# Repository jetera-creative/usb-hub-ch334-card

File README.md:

# usb-hub-ch334-card
USB Hub CH334 Card.

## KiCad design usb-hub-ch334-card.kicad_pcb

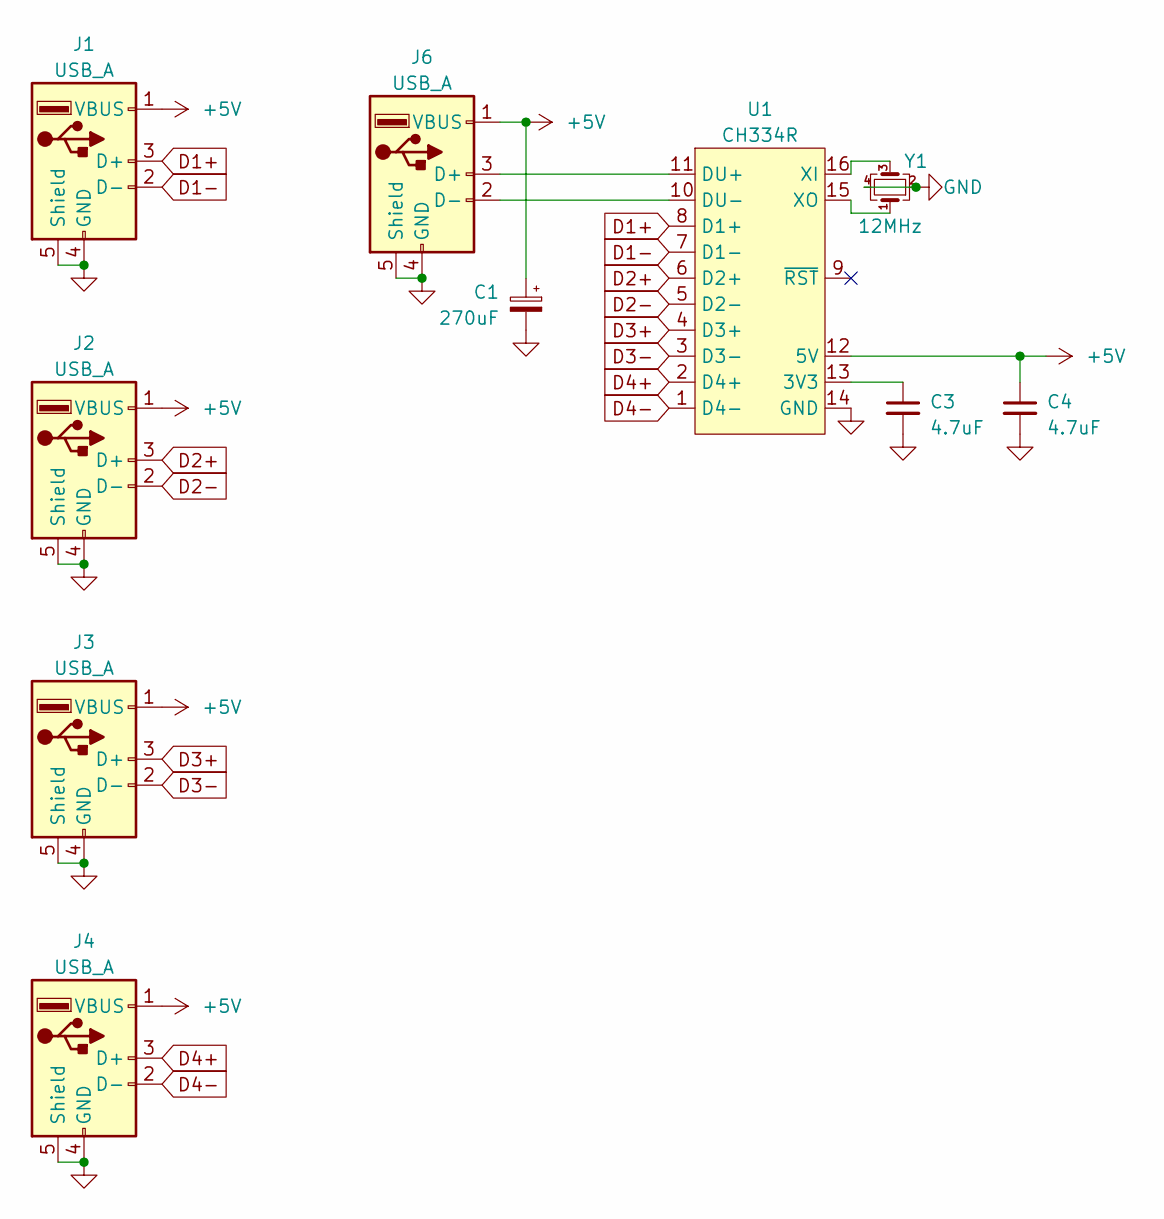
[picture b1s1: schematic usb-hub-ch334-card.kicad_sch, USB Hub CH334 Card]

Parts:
C1: 270uF; CP_Radial_D5.0mm_P2.50mm
C3, C4: 4.7uF; C_0805_2012Metric
J1, J2, J3, J4: USB_A; USB_A_Stewart_SS-52100-001_Horizontal
J6: USB_A; USB_A_Molex_48037-2200_Horizontal
U1: CH334R; QSOP-16_3.9x4.9mm_P0.635mm
Y1: 12MHz; Crystal_SMD_3225-4Pin_3.2x2.5mm

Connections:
+5V: C1.1, C4.1, J1.1 (VBUS), J2.1 (VBUS), J3.1 (VBUS), J4.1 (VBUS), J6.1 (VBUS), U1.12 (5V)
D1+: J1.3 (D+), U1.8 (D1+)
D1-: J1.2 (D-), U1.7 (D1-)
D2+: J2.3 (D+), U1.6 (D2+)
D2-: J2.2 (D-), U1.5 (D2-)
D3+: J3.3 (D+), U1.4 (D3+)
D3-: J3.2 (D-), U1.3 (D3-)
D4+: J4.3 (D+), U1.2 (D4+)
D4-: J4.2 (D-), U1.1 (D4-)
GND: C1.2, C3.2, C4.2, J1.4 (GND), J1.5 (Shield), J2.4 (GND), J2.5 (Shield), J3.4 (GND), J3.5 (Shield), J4.4 (GND), J4.5 (Shield), J6.4 (GND), J6.5 (Shield), U1.14 (GND), Y1.2, Y1.4
unnamed: J6.3 (D+), U1.11 (DU+)
unnamed: J6.2 (D-), U1.10 (DU-)
unnamed: C3.1, U1.13 (3V3)
unnamed: U1.16 (XI), Y1.3
unnamed: U1.15 (XO), Y1.1

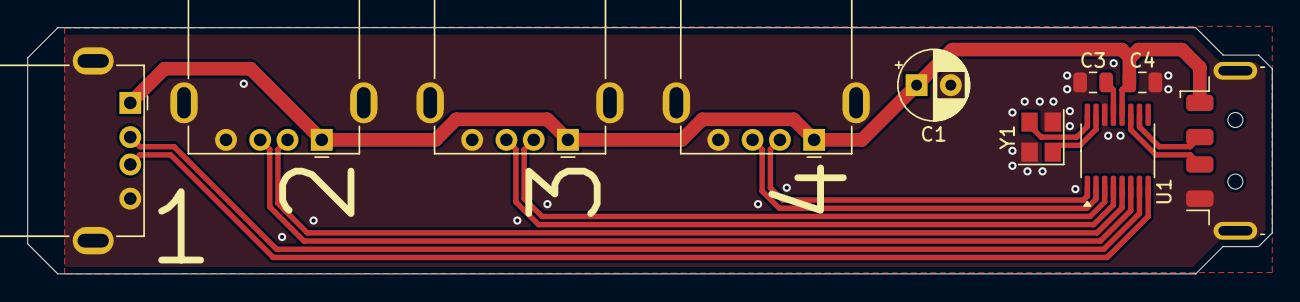
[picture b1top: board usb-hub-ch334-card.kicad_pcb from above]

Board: 2 copper layers, 91.0 x 18.0 mm, 10 parts (0 on the bottom side), 15 nets.

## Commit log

2024-07-09 Rev 1.0
2024-07-25 Rev 1.1

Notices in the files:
usb-hub-ch334-card.kicad_pcb:
© 2024 JetERA Creative
